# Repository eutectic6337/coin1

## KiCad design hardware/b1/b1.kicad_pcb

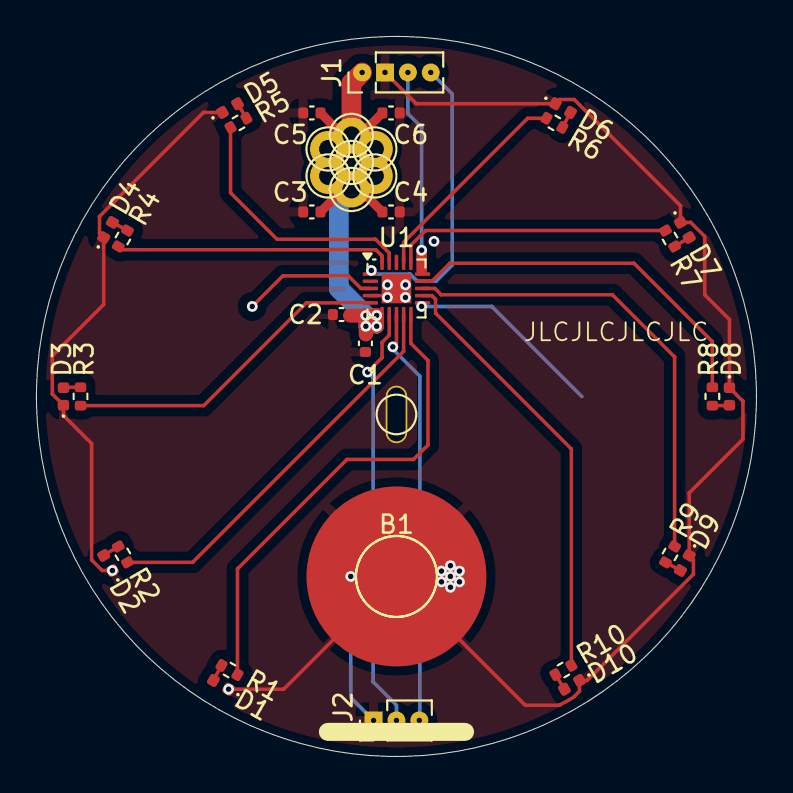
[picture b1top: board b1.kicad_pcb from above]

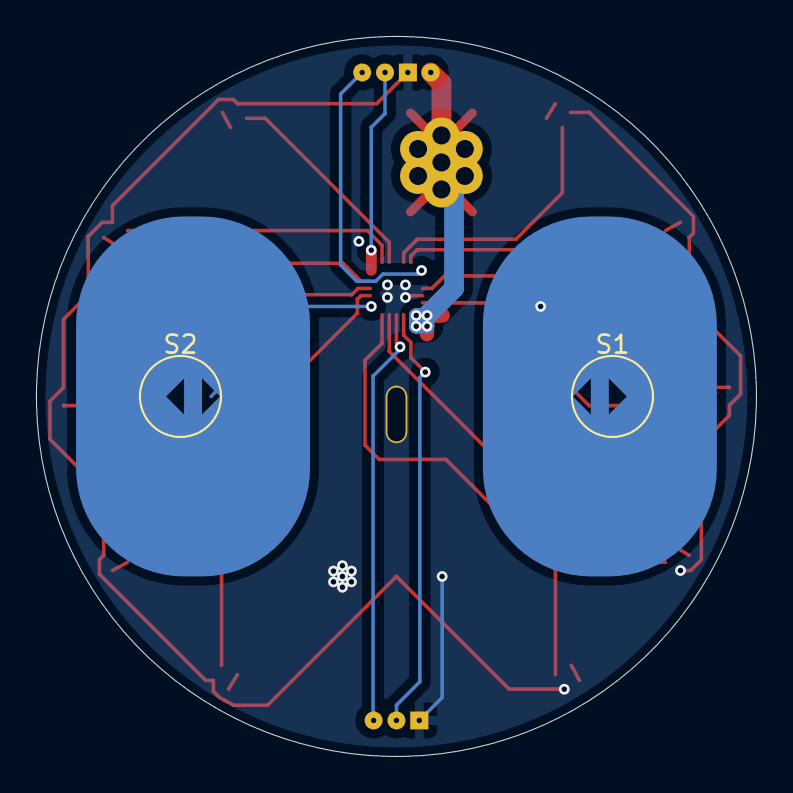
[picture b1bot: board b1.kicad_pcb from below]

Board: 2 copper layers, 40.0 x 40.0 mm, 41 parts (2 on the bottom side), 28 nets.

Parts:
-: BAT-; TestPoint_Pad_D4.0mm
B1: BAT-; TestPoint_Pad_D4.0mm
C1, C2, C3, C4, C5, C6: 10n; C_0402_1005Metric
D1, D2, D3, D4, D5, D6, D7, D8, D9, D10: LED; LED_0402_1005Metric
J1: Conn_01x04; PinHeader_1x04_P1.27mm_Vertical
J2: Conn_01x03; PinHeader_1x03_P1.27mm_Vertical
R1, R2, R3, R4, R5, R6, R7, R8, R9, R10: 47R; R_0402_1005Metric
S1, S2: touch; TestPoint_Pad_D4.0mm
T1: TestPoint_THTPad_3.0x3.0mm_Drill1.5mm
T51, T51#2, T52, T53, T54, T55, T56: TestPoint_THTPad_D2.0mm_Drill1.0mm
U1: WCH CH32V003F4U6; QFN-20-1EP_3x3mm_P0.4mm_EP1.65x1.65mm

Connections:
+3V0: C1.1, C2.1, C3.1, C4.1, C5.1, C6.1, J1.1, T51.1, T51#2.1, T52.1, T53.1, T54.1, T55.1, T56.1, U1.6 (VDD)
/LED1: R1.1, U1.10 (PC3)
/LED2: R2.1, U1.9 (PC2)
/LED3: R3.1, U1.5 (PD0)
/LED4: R4.1, U1.20 (PD6)
/LED5: R5.1, U1.19 (PD5)
/LED6: R6.1, U1.17 (PD3)
/LED7: R7.1, U1.16 (PD2)
/LED8: R8.1, U1.14 (PC7)
/LED9: R9.1, U1.13 (PC6)
/LED10: R10.1, U1.12 (PC5)
/NRST: J1.4, U1.1 (NRST)
/RX: J2.3, U1.8 (USART_RX_3)
/SWIO: J1.3, U1.15 (SWIO)
/TX: J2.2, U1.7 (USART_TX_3)
/touch1: S1.1, U1.3 (ADC_IN0)
/touch2: S2.1, U1.11 (ADC_IN2)
GND: -.1, B1.1, C1.2, C2.2, C3.2, C4.2, C5.2, C6.2, D1.1 (K), D2.1 (K), D3.1 (K), D4.1 (K), D5.1 (K), D6.1 (K), D7.1 (K), D8.1 (K), D9.1 (K), D10.1 (K), J1.2, J2.1, T1.1, U1.4 (VSS), U1.21 (VSS)
unnamed: D1.2 (A), R1.2
unnamed: D2.2 (A), R2.2
unnamed: D3.2 (A), R3.2
unnamed: D4.2 (A), R4.2
unnamed: D5.2 (A), R5.2
unnamed: D6.2 (A), R6.2
unnamed: D7.2 (A), R7.2
unnamed: D8.2 (A), R8.2
unnamed: D9.2 (A), R9.2
unnamed: D10.2 (A), R10.2

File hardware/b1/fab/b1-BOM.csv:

"Id";"Designator";"Footprint";"Quantity";"Designation";"Supplier and ref";
1;"R1,R2,R10,R8,R4,R3,R6,R5,R9,R7";"R_0402_1005Metric";10;"47R";;;
2;"D2,D1,D6,D10,D5,D9,D3,D4,D7,D8";"LED_0402_1005Metric";10;"LED";;;
3;"C6,C1,C5,C4,C3,C2";"C_0402_1005Metric";6;"10n";;;
4;"U1";"QFN-20-1EP_3x3mm_P0.4mm_EP1.65x1.65mm";1;"WCH CH32V003F4U6";;;

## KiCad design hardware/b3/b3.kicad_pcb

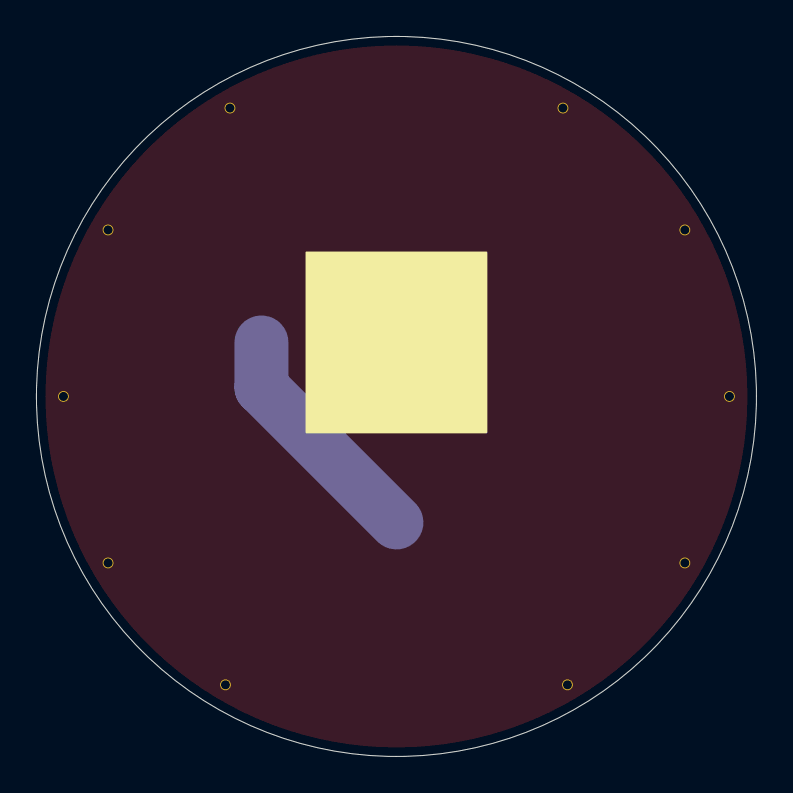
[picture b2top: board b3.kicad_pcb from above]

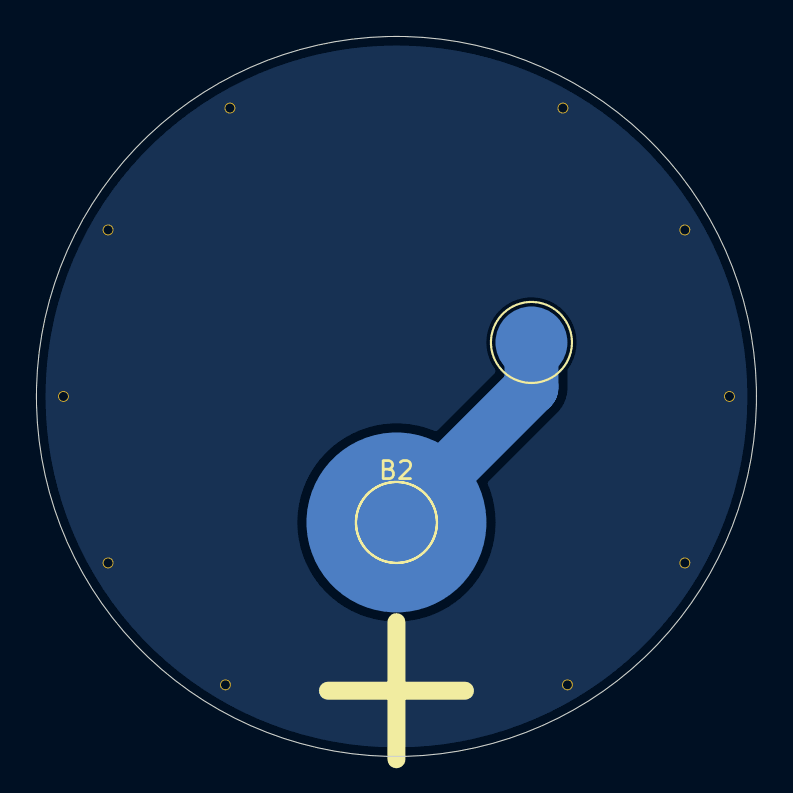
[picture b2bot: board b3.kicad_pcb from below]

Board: 2 copper layers, 40.0 x 40.0 mm, 12 parts (2 on the bottom side), 2 nets.

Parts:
+: BAT+; TestPoint_Pad_D4.0mm
B2: BAT+; TestPoint_Pad_D4.0mm
T42, T43, T44, T45, T46, T48, T49, T50, T51, T52: TestPoint_THTPad_D1.0mm_Drill0.5mm

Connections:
+3V0: +.1, B2.1
GND: T42.1, T43.1, T44.1, T45.1, T46.1, T48.1, T49.1, T50.1, T51.1, T52.1
